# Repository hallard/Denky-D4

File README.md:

# Denky D4 ESP32 Teleinfo

This board is used to get French energy meter called Teleinfo (AKA TIC) and has the following features:

- Steroid ESP32 using ESP32-PICO-V3-02 chip with 8Mb Flash and 2Mb PSRAM
- Serial to USB onboard converter
- Teleinfo Reader interface
- RGB User Led
- Blue LED to see if Teleinfo signal is received
- QWIIC/STEMMA I2C header sensors connector
- USB-C Connector

It is a plug and play board, nothing to solder or assemble.

# History

**New in v1.3a**

- Changed TIC trimmer from 1K to 2K
- Changed TIC Led (blue) resistor to decrease light intensity
- Placed easy cutting trace to disable Teleinfo Blue LED
- Added exposed pad for 5V and GND to external powering out of USB connector

**v1.3**

- Changed some silk for better reading

**v1.2**

- Replaced R3 by a trimmer to allow TIC sensitivity change without soldering resistors

**v1.1**

- Changed CPU now use ESP32-PICO-V3-02 with 8Mb Flash and 2Mb PSRAM
- Changed USB/SERIAL chip to CH9102 due to shortage
- Added footprint for U-FL connector for external antenna 
- Removed headers pins
- Reduced RGB LED size using SK6805-1515
- Added small visual blue LED on Teleinfo receive signal
- All components on same side (nothing on bottom side)

**v1.0**

- First fully working prototype

# Detailed Description

Look at the schematics for more informations, easy to understand. Wiring is as follow:

| Pin Function | ESP32-PICO | 
|  :---        |  :---:  | 
| Téléinfo Rx  |  GPIO8  | 
| RGB Led      |  GPIO14 | 
| I2C SDA      |  GPIO21 | 
| I2C SDL      |  GPIO22 | 

# Schematics

# Boards

# Firmware 

It's compatible with Arduino IDE, Visual Studio Code and also Micro Python since this board use same CPU than Adafruit [QT-PY-ESP32-PICO](https://learn.adafruit.com/adafruit-qt-py-esp32-pico)

You can write your own and use with [LibTeleinfo](https://github.com/hallard/LibTeleinfo) library I wrote if you want to get rid of driving teleinfo stuff (chekout some [examples](ttps://github.com/hallard/LibTeleinfo/tree/master/examples)).

## Tasmota

But I strongly suggest using amazing [Tasmota](https://tasmota.github.io/docs/) firmware, all is already done and well done.

Please check Teleinfo official tasmota [documentation](https://tasmota.github.io/docs/Teleinfo/) so see how to configure your device depending on smartmeter type and what options you need.

### Nicolas's builds

Nicolas @NicolasBernaerts has made awesome changes on Tasmota to be able to show graph of consumption, history and other great features such has:

- Ecowatt server to publish RTE Ecowatt signals
- TCP server to live stream teleinfo data
- FTP server to easily retrieve graph data

You can find more information on his dedicated [repo](https://github.com/NicolasBernaerts/tasmota/tree/master/teleinfo) and also ready made build for this Denky D4 board.

### Tasmota Unofficial builds

Teleinfo is not member of official Tasmota builds. So you need to build your own with `USE_TELEINFO` define. 
But Tasmota team agreed it's not simple to build for end users, and they now provide unofficial build that follow developement branch, this mean you always have an up to date build with latest code available. Of course we added Teleinfo (ESP8266 and ESP32) builds in this unofficial build process so you have nothing to install and compile/link (building). You can't go easier.

And as a cherry on the cake, easy flasher tools (web version and executable one) will present Teleinfo firmware so you are able to flash teleinfo firmware in less than 1 minute. You can check detail [here](https://github.com/Jason2866/Tasmota-specials) but here how to do that.

- Launch [Web Flasher here](https://jason2866.github.io/Tasmota-specials/) 
- Select Teleinfo 
- Select Serial port, and click `install`

Once done something like that

After flashed, you should now see a new access point named `tasmota_aabbcc_xxxx` where you can connect to configure your WiFi for the device to connect on.

Alternatively, if you connect serial console and reset the device you should see Serial logs like that
```
00:00:00.003 HDW: ESP32-D0WDQ6 
00:00:00.037 UFS: FlashFS mounted with 308 kB free
00:00:00.109 CFG: Loaded from File, Count 12
00:00:00.124 QPC: Count 1
00:00:00.257 CFG: no '*.autoconf' file found
00:00:00.263 BRY: Berry initialized, RAM used=3620
00:00:00.282 BRY: no 'preinit.be'
00:00:00.291 Project tasmota - Tasmota Version 10.0.0.3(teleinfo)-2_0_1_1(2021-11-30T14:22:47)
00:00:00.379 BRY: no 'autoexec.be'
00:00:00.447 WIF: WifiManager active for 3 minutes
00:00:01.139 HTP: Web server active on tasmota-090F8C-3980 with IP address 192.168.4.1
00:00:06.827 QPC: Reset
```

If you want to deep into this process or just curious, you can check out it's [here](https://github.com/Jason2866/Tasmota-specials)

:memo: If you have some issues flashing with Web Flasher, do not hesitate to use another awesome tool [ESP Flasher](https://github.com/Jason2866/ESP_Flasher), with this one you can see exactly what's going on in case of issue because it has built in console. Usefull also after reboot of the device because console still active. This is the one I'm using day by day. In this case you need to download firmware to flash first [here](https://github.com/Jason2866/Tasmota-specials/tree/firmware/firmware/tasmota/other). Download firmware `tasmota-teleinfo`

You can take a look on `autoconf` [folder](https://github.com/tasmota/autoconf/tree/main/raw/esp32/Wemos_Teleinfo) to see some of init commands used on Denky D4.

:memo: Don't forget to reset Energy counters on first boot with console command `EnergyTotal 0` if you have erratic values. 

### I2C Display

You can add fancy I2C display (or even I2C sensors), using the on board QWIIC sensor, please refer to section [I2C Display](https://github.com/hallard/WeMos-TIC/blob/master/README.md#i2c-display).

### Autoconf 

Another awesome feature of Tasmota is the ability to download configuration profile, and guess what, we done it for Denky D4, just go to configuration option, select Autoconfig and then choose in the list `Denky D4 V1.1` and here you are, ne need to copy/paste template, it's done by autoconfig.
If you want to deep into this process or just curious, you can check out it's [here](https://github.com/tasmota/autoconf)

### Tasmota template

I strongly suggest using awesome Tamsota autoconf feature but if you need Tasmota template for Denky D4, here it it

#### V1.1 and up
```json
{"NAME":"Denky D4 (v1.1)","GPIO":[32,0,0,0,1,0,0,0,0,1,1376,1,0,0,0,0,0,640,608,0,0,0,0,0,0,0,5632,0,0,0,0,0,0,0,0,0],"FLAG":0,"BASE":1}
```

#### V1.0
```json
{"NAME":"Denky D4 (v1.0)","GPIO":[32,0,0,0,1,0,0,0,0,1,0,1,0,0,0,0,0,640,608,0,0,450,449,448,0,0,5632,0,0,0,0,0,0,0,0,0],"FLAG":0,"BASE":1}
```

## Berry Scripting 

Now you can personalize code with [Berry language](https://tasmota.github.io/docs/Berry/). Check out some Berry samples [here](https://github.com/arendst/Tasmota/blob/development/tasmota/berry/examples/)

You can do that by going to Berry console from Tasmota WEB user interface.

### Drive RGB LED depending on actual power

Here is a Berry example, goal is to follow real time consumption driving on board RGB Led depending on current Power consumption (low green then going to red when reaching maximum current of your contract)

```python
#-
# example of using Berry script to change the led color
# accordingly to power consumption
# using Denky or WeMos Teleinfo (French Teleinfo reader)
-#

#- define the global symbol for reference -#
runcolor = nil

def runcolor()
  var max_contrat = 30 # contrat 30A
  var i = energy.current
  #print(i)
  var red = tasmota.scale_uint(int(i), 0, max_contrat, 0, 255)
  var green = 255 - red
  var channels = [red, green, 0]
  light.set({"channels":channels, "bri":64, "power":true})
  tasmota.set_timer(2000, runcolor)
end

#- run animation -#
runcolor()
```

### Send data to Emoncms with Berry 

What's magic with Berry is the ability to do basic stuff with data, in this example we will intercept MQTT send message by Energy driver, do some calc and send data to Emoncms every 15 seconds and also to drive RGB Led from Green (low load) to Red (approach max subscription)

Modifiy API key with your, and copy paste the following code into Berry Console. Tst and validate if all is okay for you.

Once all is fine, you paste the code into a file named `autoexec.be` on the Tasmota Filesystem so it will be executed each time Tasmota device starting.

#### Mode Historique (contrat heures creuses)

```python
import json

var api_url = "https://emoncms.org/input/post"
var api_key = "YOUR_EMON_API_WRITE_KEY"
var node_name = "NODE_NAME"
var post_every = 15000 # post evert 15 seconds
var payload = {}

def send_emoncms()
  # Convert JSON object to string 
  var obj_json = json.dump(payload)

  # Create URL to call
  var param="?fulljson="+obj_json + "&node="+node_name + "&apikey="+api_key 
  # Post Data to EMONCMS
  var cl = webclient()
  cl.begin( api_url + param)
  var r =  cl.GET()
  tasmota.set_timer(post_every, send_emoncms)
end

def setcolor(iinst, isousc)
  var red = tasmota.scale_uint(iinst, 0, isousc, 0, 255)
  var green = 255 - red
  var channels = [red, green, 0]
  light.set({"channels":channels, "bri":64, "power":true})
end

# set global payload the field we need
def rule_tic(value, trigger)
  # Got Heures Creuses contract so I will calculate total consumption
  # adding Heures Creuses (HCHC) + Heures Pleines (HCHP) and create new value for emoncms 
  # Change label depending on name for your contract type
  var htot = value['HCHP'] + value['HCHC'] # mode historique
  # Create new value HTOT converted to kWH
  payload['HTOT'] = htot / 1000.0
  # Calculate current percent Load 
  var iinst = value['IINST']  # mode historique
  var isousc= value['ISOUSC'] # mode historique

  if iinst != nil && isousc != nil 
    # Drive RGB LED
    setcolor(iinst, isousc)
    if isousc > 0
      load = 100 * iinst / isousc
      payload['LOAD'] = load
    end
  end

  # Set values we need to send to emoncms
  payload['ADCO']  = value['ADCO']
  payload['HCHP']  = value['HCHP']
  payload['HCHC']  = value['HCHC']
  payload['ISOUSC']= isousc
  payload['PAPP']  = value['PAPP']
  payload['IINST'] = iinst

end

def start()
  # Callback on each frame interception
  tasmota.add_rule("TIC",rule_tic)
  # fire 1st post in 5s 
  tasmota.set_timer(5000, send_emoncms)
end

# delay start to have time to get full frame
tasmota.set_timer(10000, start)

```

#### Mode Standard (contrat heures creuses)

```python
import json

var api_url = "https://emoncms.org/input/post"
var api_key = "YOUR_EMON_API_WRITE_KEY"
var node_name = "NODE_NAME"
var post_every = 15000 # post evert 15 seconds
var payload = {}

def send_emoncms()
  # Convert JSON object to string 
  var obj_json = json.dump(payload)

  # Create URL to call
  var param="?fulljson="+obj_json + "&node="+node_name + "&apikey="+api_key 
  # Post Data to EMONCMS
  var cl = webclient()
  cl.begin( api_url + param)
  var r =  cl.GET()
  tasmota.set_timer(post_every, send_emoncms)
end

def setcolor(iinst, isousc)
  var red = tasmota.scale_uint(iinst, 0, isousc, 0, 255)
  var green = 255 - red
  var channels = [red, green, 0]
  light.set({"channels":channels, "bri":64, "power":true})
end

# set global payload the field we need
def rule_tic(value, trigger)
  # Got Heures Creuses contract so I will calculate total consumption
  # Calculate current percent Load 
  var iinst = value['IRMS1']  
  var isousc= value['PREF']*5 

  if iinst != nil && isousc != nil 
    # Drive RGB LED
    setcolor(iinst, isousc)
    if isousc > 0
      load = 100 * iinst / isousc
      payload['LOAD'] = load
    end
  end

  # Here I keep name of historique mode
  payload['ADCO']  = value['ADSC']
  payload['HTOT']  = value['EAST'] / 1000 # I need kWh
  payload['HCHP']  = value['EASF01']
  payload['HCHC']  = value['EASF02']
  payload['ISOUSC']= isousc
  payload['PAPP']  = value['SINSTS']
  payload['IINST'] = iinst

end

def start()
  # Callback on each frame interception
  tasmota.add_rule("TIC",rule_tic)
  # fire 1st post in 5s 
  tasmota.set_timer(5000, send_emoncms)
end

# delay start to have time to get full frame
tasmota.set_timer(10000, start)

```

### Custom WEB Interface

If you are not happy with values on the WEB interface you can totaly change them to fit your needs.

You can add new values to display or disable all values displayed and use you own or even some calculated ones.

To disable all current values displayed please use the following command in console (not the berry one)

```
backlog0 WebSensor0 0 ; WebSensor1 0 ; WebSensor2 0 ; WebSensor3 0
```

Then you can add Teleinfo driver (this one as example) into a file named `teleinfo.be`

This is just an example please fill it to your needs. This one display Total `EAST` index, `URMS1` and `IRMS1` on web interface

```python
# Teleinfo driver written in Berry
# Support for Teleinfo custom values from choosen fields returned by smart meter
 
class TELEINFO: Driver

  # Global var Needed
  var east
  var irms
  var urms

  def init()
    # initialize globals

    # Don't display original sensors on WebUI, we want just our ones
    tasmota.cmd("backlog0 WebSensor0 0 ; WebSensor1 0 ; WebSensor2 0 ; WebSensor3 0")

    # create rules to trigger when Teleinfo values updates 
    # Use Teleinfo Etiquette Names to get whatever value you need
    tasmota.add_rule("TIC#EAST", /value -> self.trigger_east(value))
    tasmota.add_rule("TIC#IRMS1", /value -> self.trigger_irms(value))
    tasmota.add_rule("TIC#URMS1", /value -> self.trigger_urms(value))
  end

  def trigger_east(index)
    self.east = index
  end

  def trigger_irms(i)
    self.irms = i
    # DEBUG print("irms:", i)
  end

  def trigger_urms(u)
    self.urms = u
    # DEBUG print("urms:", u)
  end

  # trigger a read every second 
  def every_second()
    # DEBUG print("sensors:",tasmota.read_sensors())
  end

  # display sensor value in the web UI
  def web_sensor()
    import string
    var msg = string.format(
            "{s}Consommation{m}%d Wh{e}"
            "{s}Tension RMS{m}%d V{e}"
            "{s}Intensité RMS{m}%d A{e}", 
             self.east, self.urms, self.irms )

    tasmota.web_send_decimal(msg)
  end

end

# Instantiate the driver
teleinfo = TELEINFO()
# add it to Tasmota
tasmota.add_driver(teleinfo)

```

Then you need to load and start it into your `autoexec.be` file. just add followin at the end of the file

```python
# Auto start teleinfo driver
load("teleinfo.be")
```

#### Here how it looks like

### ESPHome

Denky D4 is fully compatible with ESPHome, find below a sample for Historique with Heures Creuses contract.
Pasting this code without knowing your contract and teleinfo mode of your linky will just NOT work, you need to adpat to your needs        

Read and get full working samples on @mathieucarbou [gist](https://gist.github.com/mathieucarbou/886d2a6f5c0b51bb261d6a1329beb08d#file-readme-md)

`denky-d4.yaml`

```yaml
# This code comes from @mathieucarbou many thanks to him
# you need to check it out and adapt depending on your needs
# https://gist.github.com/mathieucarbou/886d2a6f5c0b51bb261d6a1329beb08d#file-readme-md
# You need to knw wich mode your smart meter is (HISTORIQUE or STANDARD)
# and which contract you have to adjust sensor name to grab correct sensor information

esphome:
  name: denky-d4
  friendly_name: Denky D4

esp32:
  board: denky_d4
  framework:
    type: esp-idf

logger:
#  level: WARN

wifi:
  ssid: !secret wifi_ssid
  password: !secret wifi_password

api:

ota:
  platform: esphome

# Denky D4 RX pin
uart:
  rx_pin:
    number: GPIO8
    ignore_pin_validation_error: true
  baud_rate: 1200
  parity: EVEN
  data_bits: 7
  stop_bits: 1

binary_sensor:
  - platform: status
    id: teleinfo_status
    name: "Teleinfo Status"

button:
  - platform: restart
    name: "Teleinfo Restart"

# https://esphome.io/components/sensor/teleinfo.html
teleinfo:
  update_interval: 5s
  historical_mode: true

# Web Server: https://esphome.io/components/web_server.html
web_server:
  local: true
  port: 80    
    #   auth:
    #     username: !secret esphome_web_server_username
    #     password: !secret esphome_web_server_password

# https://esphome.io/components/sensor/index.html
sensor:
  # WiFi
  - platform: wifi_signal
    name: "WiFi Signal"
    unit_of_measurement: dB
    device_class: signal_strength
    accuracy_decimals: 0
    update_interval: 60s
  # Uptime
  - platform: uptime
    name: "Uptime"
    unit_of_measurement: s
    device_class: duration
    accuracy_decimals: 0
    update_interval: 60s

#######################################################
#      HISTORIQUE with Heures Creuses Contract        #
# Pasting this code without knowing your contract and #
# teleinfo mode of your linky will just NOT work      #
# YOu will need to adpat to your needs                #
#######################################################

  # Intensité souscrite
  - platform: teleinfo
    tag_name: "ISOUSC"
    name: "Intensité souscrite"
    unit_of_measurement: A
    device_class: current
    state_class: measurement
  # Index option Base
  #- platform: teleinfo
  # tag_name: "BASE"
  # name: "Index Base"
  # unit_of_measurement: kWh
  # device_class: energy
  # state_class: total_increasing
  # accuracy_decimals: 3
  # filters:
  #   - multiply: 0.001
  # Index option HP/HC
  - platform: teleinfo
    tag_name: "HCHC"
    name: "Index HC"
    unit_of_measurement: kWh
    device_class: energy
    state_class: total_increasing
    accuracy_decimals: 3
    filters:
      - multiply: 0.001
  - platform: teleinfo
    tag_name: "HCHP"
    name: "Index HP"
    unit_of_measurement: kWh
    device_class: energy
    state_class: total_increasing
    accuracy_decimals: 3
    filters:
      - multiply: 0.001

  # Intensité Instantanée (monophasé)
  - platform: teleinfo
    tag_name: "IINST"
    name: "Intensité Instantanée"
    unit_of_measurement: A
    device_class: current
    state_class: measurement
  # Avertissement de Dépassement De Puissance Souscrite
  - platform: teleinfo
    tag_name: "ADPS"
    name: "Intensité Instantanée Dépassement"
    unit_of_measurement: A
    device_class: current
    state_class: measurement
  # Intensité maximale appelée (monophasé)
  - platform: teleinfo
    tag_name: "IMAX"
    name: "Intensité Maximale"
    unit_of_measurement: A
    device_class: current
    state_class: measurement
  # Puissance apparente
  - platform: teleinfo
    tag_name: "PAPP"
    name: "Puissance Apparente"
    unit_of_measurement: VA
    state_class: measurement
    device_class: apparent_power

# https://esphome.io/components/text_sensor/index.html
text_sensor:
  # Adresse du compteur
  - platform: teleinfo
    tag_name: "ADCO"
    name: "Adresse"
  # Option tarifaire choisie
  - platform: teleinfo
    tag_name: "OPTARIF"
    name: "Option Tarifaire"
  # Période Tarifaire en cours
  - platform: teleinfo
    tag_name: "PTEC"
    name: "Période Tarifaire"
  # Couleur du lendemain
  - platform: teleinfo
    tag_name: "DEMAIN"
    name: "Couleur Demain"
  # Horaire Heures Pleines Heures Creuses
  - platform: teleinfo
    tag_name: "HHPHC"
    name: "Horaire HP/HC"
  # Mot d'état du compteur
  - platform: teleinfo
    tag_name: "MOTDETAT"
    name: "Mot d'état"

```

# Support and discussion

If you have any issue or just want to discuss on this project, please use community [forum](https://community.ch2i.eu/category/20)

# License

This work is licensed under a [Creative Commons Attribution-NonCommercial-ShareAlike 4.0 International License](https://creativecommons.org/licenses/by-nc-sa/4.0/)    
If you want to do commercial stuff with this project, please contact [CH2i company](https://ch2i.eu/en#support) so we can organize an simple agreement.

# Lazy building your own? 

You can order this module (V1.3a only) fully assembled with some extra on [tindie][1] or on [Lectronz](https://lectronz.com/products/denky-d4).

European customers may prefer ordering on Lectronz, which offers additional payment methods and pricing in Euros.

# Misc

See news and other projects on my [blog][2] 
 
[1]: https://www.tindie.com/products/25467/
[2]: https://hallard.me

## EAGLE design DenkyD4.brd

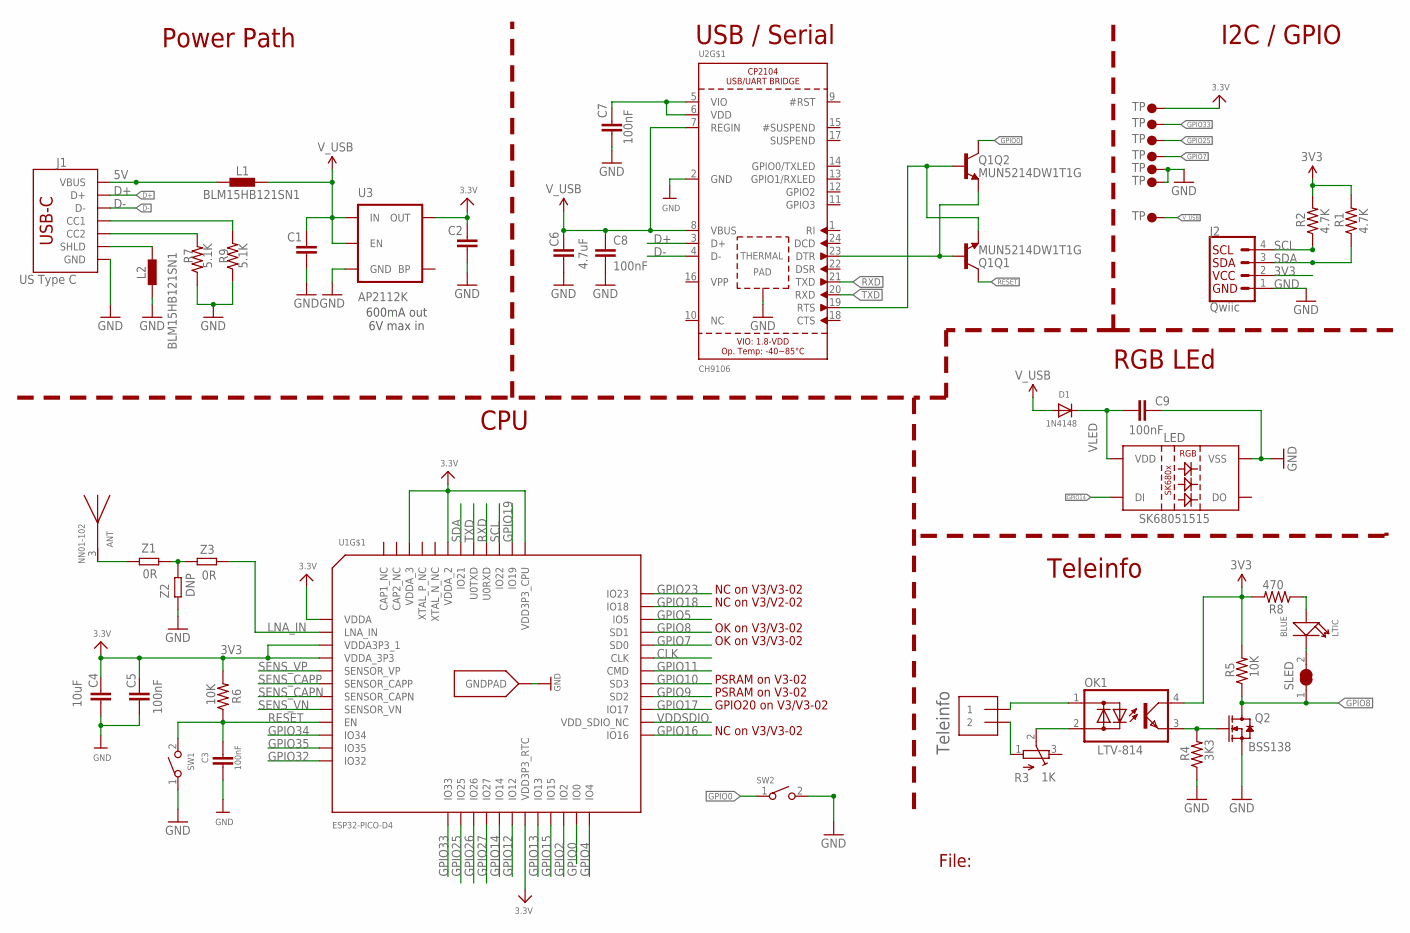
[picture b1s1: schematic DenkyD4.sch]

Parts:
ANT: NN01-102; XCVR_NN03-320
C1, C2: 1.0uF; 0402-CAP-OK
C3, C5, C7, C8, C9: 100nF; 0402-CAP-OK
C4: 10uF; 0402-CAP-OK
C6: 4.7uF; 0402-CAP-OK
D1: 1N4148; SOD-523
J1: US Type C; USB-C-16P-4LAYER-ISOLATED
J2: Qwiic; JST04_1MM_VERT
J3: KF2EDGR-3.81-2P; 1X2-3.5MM
L1, L2: BLM15HB121SN1; 0402
LED: SK68051515; SK6805-1515
LTIC: BLUE; LED-0402
OK1: LTV-814; DIL4-SMD
Q1: MUN5214DW1T1G; DUAL_NPN_SC70-6
Q2: BSS138; SOT-323-3
R1, R2: 4.7K; 0402-RES
R3: 1K; TC33X
R4: 3K3; 0402-RES
R5, R6: 10K; 0402-RES
R7, R9: 5.1K; 0402-RES
R8: 470; 0402-RES
SLED: SOLDERJUMPER_CLOSED; SOLDERJUMPER_CLOSEDWIRE
SW1: RESET; C498294
SW2: SMD-BUTTON(2P-3.0X2.5X1.2+0.4MM); C498294
TGG, TGG1, TGG2: TP3; TP60_BOT
TP3: TP3; TP60_BOT
U1: ESP32-PICO-D4; PICO-D4-QFN48
U2: CH9106; QFN24_4MM_SMSC
U3: AP2112K; SOT23-5
U$3, U$6, U$11: TP3; TP60_BOT
Z1, Z3: 0R; 0603-MATCHNET
Z2: DNP; 0603-MATCHNET

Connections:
3V3: C2.1, C4.1, C5.1, J2.2, OK1.4 (C), R1.2, R2.2, R5.2, R6.2, R8.2, TP3.P$1, U1.1 (VDDA), U1.3 (VDDA3P3_1), U1.4 (VDDA_3P3), U1.19 (VDD3P3_RTC), U1.37 (VDD3P3_CPU), U1.43 (VDDA_2), U1.46 (VDDA_3), U3.5 (OUT)
5V: J1.VBUS1 (VBUS), J1.VBUS2 (VBUS), L1.1
CLK: U1.31 (CLK)
D+: J1.A6 (D+), J1.B6 (D+), U2.3 (D+)
D-: J1.A7 (D-), J1.B7 (D-), U2.4 (D-)
DTR: Q1.1 (E), Q1.5 (B), U2.23 (DTR)
GND: C1.2, C2.2, C3.2, C4.2, C5.2, C6.1, C7.1, C8.2, C9.2, J1.GND, J1.GND2 (GND), J2.1, L2.2, LED.4 (VSS), Q2.2 (S), R4.1, R7.1, R9.1, SW1.1, SW2.2, TGG.P$1, TGG1.P$1, U1.EXP (GNDPAD), U2.2 (GND), U2.THERM (TP), U3.2 (GND), Z2.2
GPIO0: Q1.6 (C), SW2.1, U1.23 (IO0)
GPIO2: U1.22 (IO2)
GPIO4: U1.24 (IO4)
GPIO5: U1.34 (IO5)
GPIO7: U1.32 (SD0), U$3.P$1
GPIO8: Q2.3 (D), R5.1, SLED.1, U1.33 (SD1)
GPIO9: U1.28 (SD2)
GPIO10: U1.29 (SD3)
GPIO11: U1.30 (CMD)
GPIO12: U1.18 (IO12)
GPIO13: U1.20 (IO13)
GPIO14: LED.1 (DI), U1.17 (IO14)
GPIO15: U1.21 (IO15)
GPIO16: U1.25 (IO16)
GPIO17: U1.27 (IO17)
GPIO18: U1.35 (IO18)
GPIO19: U1.38 (IO19)
GPIO23: U1.36 (IO23)
GPIO25: U1.14 (IO25), U$11.P$1
GPIO26: U1.15 (IO26)
GPIO27: U1.16 (IO27)
GPIO32: U1.12 (IO32)
GPIO33: U1.13 (IO33), U$6.P$1
GPIO34: U1.10 (IO34)
GPIO35: U1.11 (IO35)
LNA_IN: U1.2 (LNA_IN), Z3.2
unnamed: Z1.1, Z2.1, Z3.1
unnamed: OK1.3 (E), Q2.1 (G), R4.2
unnamed: OK1.2 (AC2), R3.2 (S)
unnamed: J3.1, OK1.1 (AC1)
unnamed: J3.2, R3.1 (A)
unnamed: LTIC.-, SLED.2
unnamed: C7.2, U2.5 (VIO), U2.6 (VDD)
unnamed: LTIC.+, R8.1
unnamed: J1.A5 (CC1), R9.2
unnamed: J1.B5 (CC2), R7.2
unnamed: ANT.3, Z1.2
RESET: C3.1, Q1.3 (C), R6.1, SW1.2, U1.9 (EN)
RTS: Q1.2 (B), Q1.4 (E), U2.19 (RTS)
RXD: U1.40 (U0RXD), U2.21 (TXD)
SCL: J2.4, R2.1, U1.39 (IO22)
SDA: J2.3, R1.1, U1.42 (IO21)
SENS_CAPN: U1.7 (SENSOR_CAPN)
SENS_CAPP: U1.6 (SENSOR_CAPP)
SENS_VN: U1.8 (SENSOR_VN)
SENS_VP: U1.5 (SENSOR_VP)
SHIELD: J1.SHLD1 (SHLD), J1.SHLD2 (SHLD), J1.SHLD3 (SHLD), J1.SHLD4 (SHLD), J1.SHLD5 (SHLD), J1.SHLD6 (SHLD), J1.SHLD7 (SHLD), J1.SHLD8 (SHLD), L2.1
TXD: U1.41 (U0TXD), U2.20 (RXD)
VDDSDIO: U1.26 (VDD_SDIO_NC)
VLED: C9.1, D1.K (C), LED.2 (VDD)
V_USB: C1.1, C6.2, C8.1, D1.A, L1.2, TGG2.P$1, U2.7 (REGIN), U2.8 (VBUS), U3.1 (IN), U3.3 (EN)

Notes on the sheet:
File:
Teleinfo
I2C / GPIO
600mA out 6V max in
GPIO20 on V3/V3-02
NC on V3/V3-02
PSRAM on V3-02
OK on V3/V3-02
NC on V3/V2-02
RGB LEd
USB / Serial
Power Path
CPU

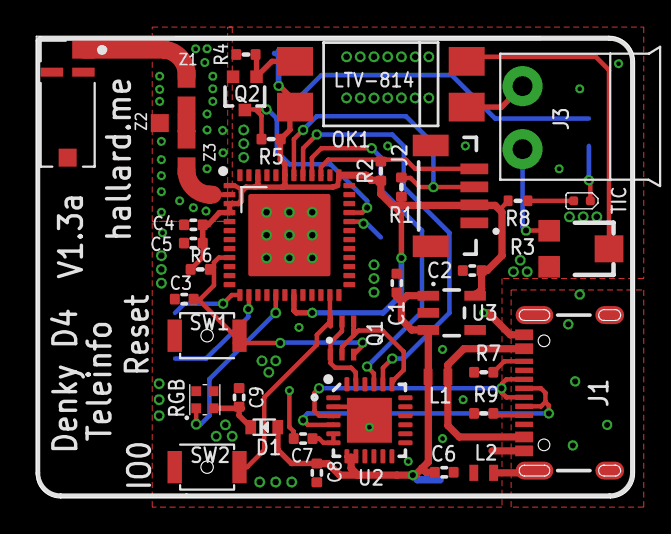
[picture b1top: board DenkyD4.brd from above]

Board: 2 copper layers, 33.2 x 25.7 mm, 46 parts (1 on the bottom side), 33 nets.

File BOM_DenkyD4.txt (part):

Partlist exported from /Users/charles/OneDrive/devt/github/_Eagle/_Teleinfo/DenkyD4/DenkyD4.sch at 15/03/2021 13:17

Qty Value                  Device                                            Package                   Parts    Description                                                                                                                                                    AVAILABILITY DESCRIPTION                                                                                                                                        MF                    MP        MPN              OC_FARNELL OC_NEWARK PACKAGE     PRICE PROD_ID     PURCHASE-URL                                               VALUE           
1                          SWITCH_TACT_SMT4.6X2.8                            BTN_KMR2_4.6X2.8          B1       SMT Tact Switches                                                                                                                                                                                                                                                                                                                                                                                                                                                                                             
2   0.1uF                  CAP0402-CAP-OK                                    0402-CAP-OK               C3, C5   Capacitor                                                                                                                                                                                                                                                                                                                                                                                                                                                                                                     
2   0R                     RESISTOR0603-RES                                  0603-RES                  R13, R14 Resistor                                                                                                                                                                                                                                                                                                                                                                                                                                                                                                      
2   1.0uF                  CAP0402-CAP-OK                                    0402-CAP-OK               C1, C2   Capacitor                                                                                                                                                                                                                                                                                                                                                                                                                                                                                                     
1   100K                   RESISTOR0402-RES                                  0402-RES                  R7       Resistor                                                                                                                                                                                                                                                                                                                                                                                                                                                                                                      
2   100nF                  CAP0402-CAP-OK                                    0402-CAP-OK               C7, C10  Capacitor                                                                                                                                                                                                                                                                                                                                                                                                                                                                                                     
1   10K                    RESISTOR0402-RES                                  0402-RES                  R6       Resistor                                                                                                                                                                                                                                                                                                                                                                                                                                                                                                      
1   10k                    RESISTOR0402-RES                                  0402-RES                  R5       Resistor                                                                                                                                                                                                                                                                                                                                                                                                                                                                                                      
1   10uF                   CAP0402-CAP-OK                                    0402-CAP-OK               C4       Capacitor                                                                                                                                                                                                                                                                                                                                                                                                                                                                                                     
2   150                    RESISTOR0402-RES                                  0402-RES                  RB, RG   Resistor                                                                                                                                                                                                                                                                                                                                                                                                                                                                                                      
1   1X2-3.5MM              1X2-3.5MM                                         1X2-3.5MM                 TINFO    3.5mm Terminal block                                                                                                                                                                                                                                                                                                                                                                                                                                                                                          
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
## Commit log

2021-04-20 renamed jpeg to jpg
2021-04-20 replace 220Ohm R3 from 0402 to 0603
2021-04-20 prepare to v1.1 version
2022-12-30 Creation
2022-12-30 Updated to V1.2
2022-12-30 deleted
2022-12-30 renamed
2022-12-30 Added Tasmota Template
2022-12-30 Added new pictures
2023-01-02 Bump to V1.2
2023-10-28 Bump to V1.3a
2023-10-28 Added custom UI example
2023-10-28 typo
2023-10-28 remove gerbers
2023-11-19 Added Nicolas Build and Link
2026-02-11 Added ESPHome documentation and sample
    Added ESPHome documentation and sample
2026-04-26 docs: add Lectronz badges next to Tindie
2026-04-29 Switch to CC BY-NC-SA 4.0 license, add LICENSE file
2026-04-29 license: use pure CC BY-NC-SA 4.0 text for GitHub auto-detection
2026-04-29 license: add copyright header above CC BY-NC-SA 4.0 text

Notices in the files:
README.md:
License:
This work is licensed under a [Creative Commons Attribution-NonCommercial-ShareAlike 4.0 International License](https://creativecommons.org/licenses/by-nc-sa/4.0/)
If you want to do commercial stuff with this project, please contact [CH2i company](https://ch2i.eu/en#support) so we can organize an simple agreement.
parts and their libraries:
SparkFun-PowerIC: Licensing: Creative Commons ShareAlike 4.0 International - https://creativecommons.org/licenses/by-sa/4.0
